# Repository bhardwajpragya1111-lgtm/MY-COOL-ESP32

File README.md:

# ESP32 Custom Board
A custom ESP32-based development board designed and routed using EasyEDA.
This project is designed as a compact and reusable ESP32 development platform for IoT, embedded systems, automation, sensors, Wi-Fi, and Bluetooth-based projects.

## 🎥 Project Demo

Watch the complete project demonstration on YouTube:

[▶️ Watch the Demo Video](https://youtu.be/ROO8zUUU6sM)

This video demonstrates the project functionality, hardware setup, working process, and final output.

## Features

- ESP32-based custom development board
- Wi-Fi connectivity
- Bluetooth connectivity
- USB interface for programming and power
- GPIO header pins for external components
- BOOT/RESET control buttons
- Custom PCB layout and routing
- Compact development-board design
- Designed and routed in EasyEDA
- Editable PCB design file included
- 3D OBJ model included
- Gerber manufacturing files included

## Board Overview

The custom PCB contains:

- ESP32 module
- USB connector
- USB-to-serial/programming circuitry
- Power and supporting circuitry
- BOOT/RESET control buttons
- GPIO header pins
- Passive components
- Custom PCB traces and routing

## Project Files

### PCB Design

- `PCB/PCB_PCB_ESP32_2026-09-11.json` - Main EasyEDA PCB design/source file.
- `Autorouter/Autorouter_PCB_ESP32_2026-09-11.dsn` - Autorouter design file.

### 3D Model

- `3D/ESP32.obj` - 3D OBJ model of the PCB.

### Manufacturing Files

- `Gerber/Gerber_ESP32_PCB.zip` - Gerber files for PCB manufacturing.

### Images

The `Images` folder contains PCB design, routing, and 3D preview images.

## PCB Preview

### PCB Design

### PCB Routing

### Front 3D View

### Back 3D View

Build Photo: Not available yet

## Bill of Materials

[BOM.csv](BOM/BOM.md)

## Software Required

To view or modify the PCB design:

- EasyEDA

The OBJ model can be viewed using any software that supports `.obj` 3D files.

## How to Open the PCB Design

1. Download the PCB source file from the `PCB` folder.
2. Open EasyEDA.
3. Import/open the downloaded PCB design file.
4. View or modify the PCB layout in EasyEDA.
5. Check the component footprints, PCB dimensions, layers, routing, and design rules before making changes.

## How to Manufacture the PCB

### Step 1 - Download the Design

Download the PCB design file from the `PCB` folder.

You can also download the Gerber ZIP from the `Gerber` folder if you want to manufacture the PCB directly.

### Step 2 - Check the Design

Before manufacturing, verify:

- PCB dimensions
- Component footprints
- Track routing
- Drill holes
- Component orientation
- Power connections
- USB connections
- ESP32 module footprint
- GPIO headers
- Design Rule Check (DRC)

Run the DRC in EasyEDA and fix any errors before manufacturing.

### Step 3 - Generate or Use Gerber Files

The repository already contains a Gerber ZIP file in the `Gerber` folder.

The Gerber files contain the information required by a PCB manufacturer, including:

- Copper layers
- Solder mask
- Silkscreen
- Board outline
- Drill information

If you make changes to the PCB design, generate a new Gerber package from EasyEDA before ordering the PCB.

### Step 4 - Prepare the Components

Use the PCB design and component information to identify the components required for assembly.

A Bill of Materials (BOM) can be prepared containing:

- Component value
- Component/package
- Quantity
- Part number or manufacturer part number where applicable

### Step 5 - Order the PCB

Upload the Gerber ZIP file to a PCB manufacturing service.

Select the required manufacturing specifications, such as:

- PCB quantity
- Number of layers
- PCB thickness
- Surface finish
- Solder mask
- PCB color

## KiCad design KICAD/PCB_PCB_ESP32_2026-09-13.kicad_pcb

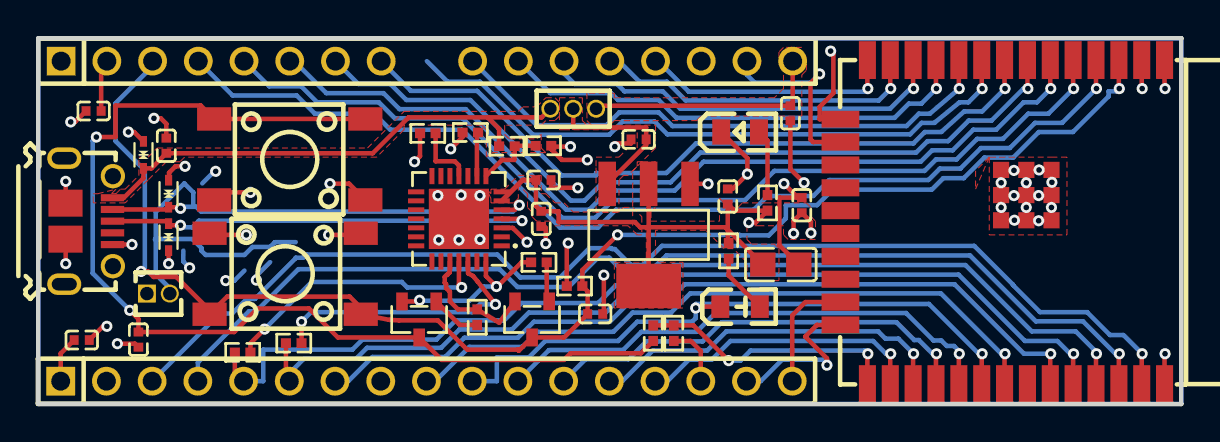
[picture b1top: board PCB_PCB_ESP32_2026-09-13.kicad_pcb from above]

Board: 2 copper layers, 63.5 x 20.3 mm, 47 parts (0 on the bottom side), 47 nets.

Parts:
C1, C2: 10uF; C0402
C3, C5, C6, C7, C8, C9, C11, C12, C13: 100nF; C0402
C4: 4.7uF; C0402
C10: 22uF; C0805
D1, D2, D3: LESD5D5.0CT1G; SOD-523_L1.2-W0.8-LS1.6-BI
J1, J2: X6511WV-17H-C30D60; HDR-TH_17P-P2.54-V-M
J3: 105017-0001; MICRO-USB-SMD_105017-0001
J5: DZ127R-11-02-25; HDR-TH_2P-P1.27-V-M
J14: 210-1S-1*3Ppin Gold-plated; HDR-TH_3P-P1.27-V-M-1
LED1: 0805G (Green); LED0805-R-RD
LED2: FC-2012HRK-620D; LED0805-RD
Q1, Q3: 2N7002T-7-F; SOT-523-3_L1.6-W0.8-P1.00-LS1.6-BR
Q2, Q4: SS8050-G; SOT-23-3_L2.9-W1.3-P1.90-LS2.4-BR
R1: 5.1kΩ; R0402
R2: 560Ω; R0402
R3, R9: 1kΩ; R0402
R4, R5: 0Ω; R0402
R6, R8, R10, R11, R13: 10kΩ; R0402
R7: 22.1kΩ; R0402
R12: 47.5kΩ; R0402
R14, R15: 22Ω; R0402
SW1, SW2: PTS645SH50SMTR92LFS; KEY-SMD_4P-L6.0-W6.0-P4.50-LS9.0
U1: AMS1117-3.3_C347222; SOT-223-4_L6.5-W3.5-P2.30-LS7.0-BR
U2: CP2102N-A02-GQFN28R; QFN-28_L5.0-W5.0-P0.50-TL-EP3.3
U3: ESP32-WROOM-32E(8MB); WIFI-SMD_ESP32-WROOM-32E

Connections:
+3V3: C2.1, C4.2, C5.1, C7.1, C8.1, C10.1, C11.1, J1.2, J2.1, J5.1, R1.1, R2.1, R3.2, R13.1, U1.2, U1.4, U2.6, U2.7, U3.2
+5V: C1.1, J14.2, U1.3
+5V_EXT: C12.1, J1.17, J14.3
+5V_VBUS: C3.1, D1.1, J3.1, J14.1, R7.1
DTR: Q4.2, R6.1, U2.28
EN: C9.1, J1.3, Q2.3, R13.2, SW1.1, SW1.2, U3.3
GND: C1.2, C2.2, C3.2, C4.1, C5.2, C6.2, C7.2, C8.2, C9.2, C10.2, C11.2, C12.2, C13.2, D1.2, D2.2, D3.2, J1.1, J1.15, J2.2, J2.8, J3.5, J3.6, J3.7, J3.8, J3.9, J3.10, LED1.2, Q1.2, Q3.2, R8.2, R11.2, R12.2, SW1.3, SW1.4, SW2.3, SW2.4, U1.1, U2.3, U2.29, U3.1, U3.15, U3.38, U3.39
I34: J1.6, U3.6
I35: J1.7, U3.7
I36: J1.4, U3.4
I39: J1.5, U3.5
IO0: R14.1, R15.1, U3.25
IO0_BTN: C13.1, Q4.3, R15.2, SW2.1, SW2.2
IO0_CON: J2.15, R14.2
IO2: J2.16, U3.24
IO4: J2.14, U3.26
IO5: J2.11, U3.29
IO12: J1.14, U3.14
IO13: J1.16, U3.16
IO14: J1.13, U3.13
IO15: J2.17, U3.23
IO16: J2.13, U3.27
IO17: J2.12, U3.28
IO18: J2.10, LED2.1, U3.30
IO19: J2.9, U3.31
IO21: J2.7, U3.33
IO22: J2.4, U3.36
IO23: J2.3, R9.1, U3.37
IO25: J1.10, U3.10
IO26: J1.11, U3.11
IO27: J1.12, U3.12
IO32: J1.8, U3.8
IO33: J1.9, U3.9
LED2_2: LED2.2, R2.2
R1_2: LED1.1, R1.2
R6_2: Q2.1, R6.2
R10_2: Q4.1, R10.2
RTS: Q2.2, R10.1, U2.24
RXD: R4.2, U2.25
RXD0: J2.6, R5.1, U3.34
TXD: R5.2, U2.26
TXD0: J2.5, R4.1, U3.35
U2_8: R7.2, R12.1, U2.8
U2_9: R3.1, U2.9
U2_11: R8.1, U2.11
USB_DN: C6.1, D2.1, J3.2, J5.2, Q1.1, Q3.1, Q3.3, R9.2, R11.1, U2.5
USB_DP: D3.1, J3.3, Q1.3, U2.4
